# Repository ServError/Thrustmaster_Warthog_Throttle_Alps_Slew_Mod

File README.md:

# Thrustmaster Warthog Throttle Alps Slew Mod

This repository houses the Thrustmaster Warthog Throttle Alps Slew Mod, an open source alternative to Thrustmaster's cheap slew joystick originally provided on the throttle.

## Is this Delta Sim's mod?

Nope, this was my 2022 mechanical, electrical, and software engineering practice project. Though the [Instructable](https://www.instructables.com/Thrustmaster-Warthog-Slew-Sensor-I2C-Upgrade/) provided a good sanity check, I started from scratch and did my own logic analysis, etc.

### Why does it look similar?

It's a bare minimum set of components fitting into a tight, keyed space while being compatible with an existing product, the only way it was going to look different was if I went out of my way to do something weird.

## How can I build it?

Let me start by stating the following: This project is mostly educational. Given the amount of parts and work it takes to build one of these, you should heavily consider buying [Delta Sim's slew mod](https://deltasimelectronics.com/products/thumbstick-slew-sensor-adapter) if you're just looking to mod your throttle and fly. Since (last I checked) it uses the same microcontroller as this project, you could even potentially switch to the firmware in this repository if you believed it to be beneficial.

### I'm still here

Alright then, You'll need to handle

- [The PCB](pcb/)
- [The Plastics](plastic/)
- [The Firmware](firmware/)

### Building

- Once the PCB is complete, program it with the firmware.

- Take 4 1.6x4mm screws and connect the frame to the PCB and take care to orient the notch correctly (see photo in plastics section).

- Connect the wire to the header.

- Unplug and pop out the original slew stick by pressing in the two clasps while pulling it outward.

- Insert the new unit into the throttle. Use notch on bottom of frame to align with notch in opening.

- Use 2 remaining screws to screw cover to frame. Do not overtighten! Screw in a good amount then install the stick.

- Check stick clearance with 2 screws and continue screwing until just barely clearing the stick.

- Connect the wire to the mainboard.

- Reassemble throttle while taking extreme care not to pinch cables between the plastic posts and throttle body. Feel free to wrap longer wires around the posts before assembling Use flashlight to triple verify clearance on other side before reinstall large screws.

- Plug in throttle and download [calibration tool with modified deadzone values](https://drive.google.com/file/d/1Ltr-QlWskVfA8-Oxs-A-aUs4HPpge5iv/view?usp=sharing). Run executable and follow instructions.

- Open Control Panel and verify stick behavior under Game Controllers.

### Drift correction / recalibration

- Download the calibration tool.

- Extract the files and edit A10_calibration.txt in a text editor.

- If the X axis is drifting, modify `Standard_DZ_SX = 0x05;` and increase 0x05 to something like 0x07. Remember to use hex values, not decimal (0x0A = 10, etc).

- Recalibrate using the exe.

- Check for drift. If still present, increase the value and calibrate again. Continue until no drift is present.

- Repeat for the Y axis by modifying `Standard_DZ_SY = 0x05;`

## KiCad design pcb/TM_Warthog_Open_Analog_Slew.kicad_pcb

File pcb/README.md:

# PCB

The PCB was designed in KiCAD and all project files are available in this repository for your tweaking pleasure.

## Ordering

For US based people, I recommend [OSH Park](https://oshpark.com/shared_projects/TJxoezw8) which can provide 3 boards for $4 to your door (which is insane!). Others will want to download the zip file from the [gerber_out](gerber_out/) folder and provide it to their PCB printing service of choice. It's possible that you'll need to download the KiCAD project and tweak the gerber settings if your printing service has any issues with the provided zip.

## Bill of Materials

| Part          | Quantity | Example Link |
| ------------- |:--------:| -----:|
| PCB           | 1        | [link](https://oshpark.com/shared_projects/TJxoezw8) |
| ATTINY441     | 1        | [link](https://www.mouser.com/ProductDetail/556-ATTINY441-SSU) |
| 100nF cap     | 1        | [link](https://www.mouser.com/ProductDetail/187-CL21B104KACNNNC) |
| 10k Ohm res   | 1        | [link](https://www.mouser.com/ProductDetail/603-RC0805FR-0710KL) |
| Joystick      | 1        | [link](https://www.mouser.com/ProductDetail/688-RKJXV122400R) |
| 1.6x4mm screw | 6        | [link](https://www.aliexpress.com/item/32968483467.html) |
| 15cm 5P cable | 1        | [link](https://www.aliexpress.com/item/32979005732.html) |
| 5P 1.25mm Header | 1        | [link](https://www.aliexpress.com/item/1005003115054198.html) |

If using the example link for the header, select the 'DIP' variety (they mean thru-hole, but oh well).

## Assembly

It's perfectly possible to construct the entire board with a soldering iron, but is certainly more convenient to install the microcontroller and passives using hot air.

If your PCB was delivered with excess material near the header side, I'd recommend filing it down for a cleaner fit.

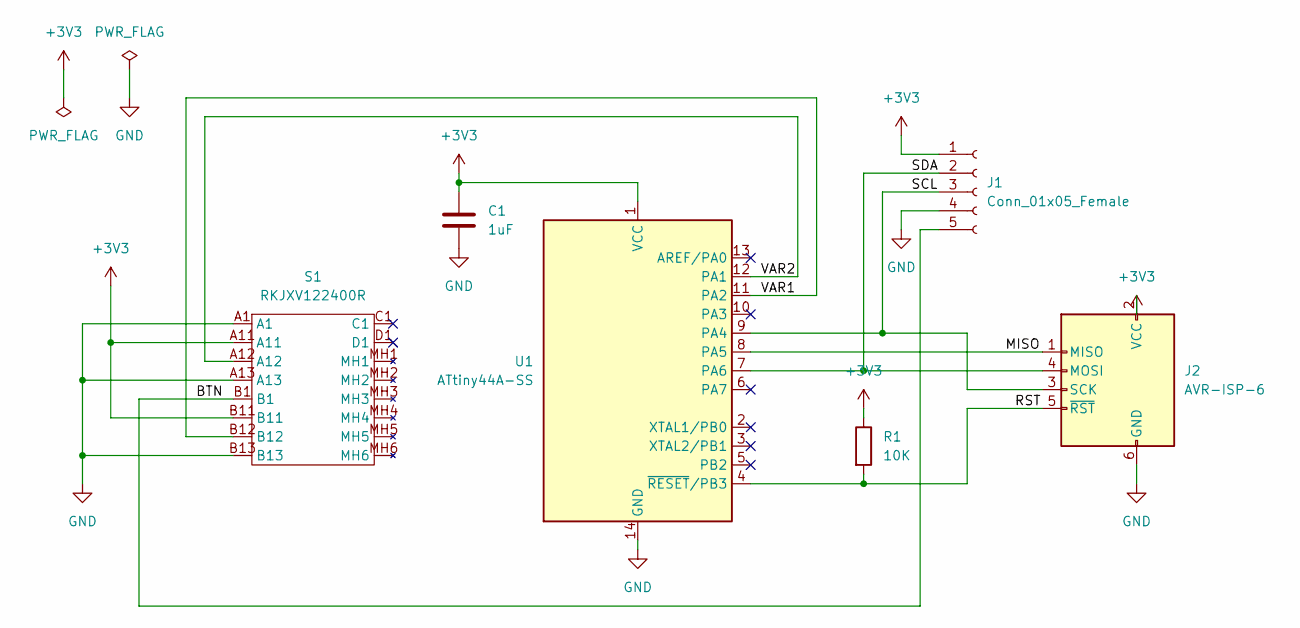
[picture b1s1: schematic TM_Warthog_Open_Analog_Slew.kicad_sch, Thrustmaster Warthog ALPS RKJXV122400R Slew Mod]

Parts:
C1: 1uF; C_0805_2012Metric
J1: Conn_01x05_Female; Molex_PicoBlade_53047-0510_1x05_P1.25mm_Vertical
J2: AVR-ISP-6; PinHeader_1x06_P1.00mm_Vertical
R1: 10K; R_0805_2012Metric
S1: RKJXV122400R
U1: ATtiny44A-SS; SOIC-14_3.9x8.7mm_P1.27mm

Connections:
+3V3: C1.1, J1.1, J2.2 (VCC), R1.1, S1.A11, S1.B11, U1.1 (VCC)
/BTN: J1.5, S1.B1
/MISO: J2.1 (MISO), U1.8 (PA5)
/RST: J2.5 (~RST), R1.2, U1.4 (~RESET/PB3)
/SCL: J1.3, J2.3 (SCK), U1.9 (PA4)
/SDA: J1.2, J2.4 (MOSI), U1.7 (PA6)
/VAR1: S1.B12, U1.11 (PA2)
/VAR2: S1.A12, U1.12 (PA1)
GND: C1.2, J1.4, J2.6 (GND), S1.A1, S1.A13, S1.B13, U1.14 (GND)

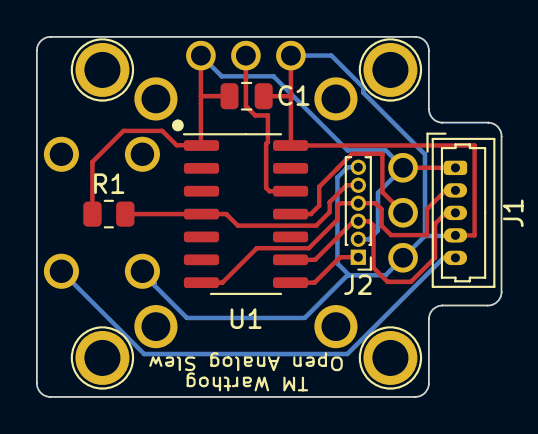
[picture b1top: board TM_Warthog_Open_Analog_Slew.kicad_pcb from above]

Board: 2 copper layers, 25.8 x 20.0 mm, 6 parts (1 on the bottom side), 9 nets.

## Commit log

2022-03-27 Initial Project Upload
2022-03-27 Fix picture link
2024-09-14 Add Windows flashing example (courtesy of StiC)
